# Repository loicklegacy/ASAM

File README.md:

# ASAM
Athmospheric Sensor Array Module

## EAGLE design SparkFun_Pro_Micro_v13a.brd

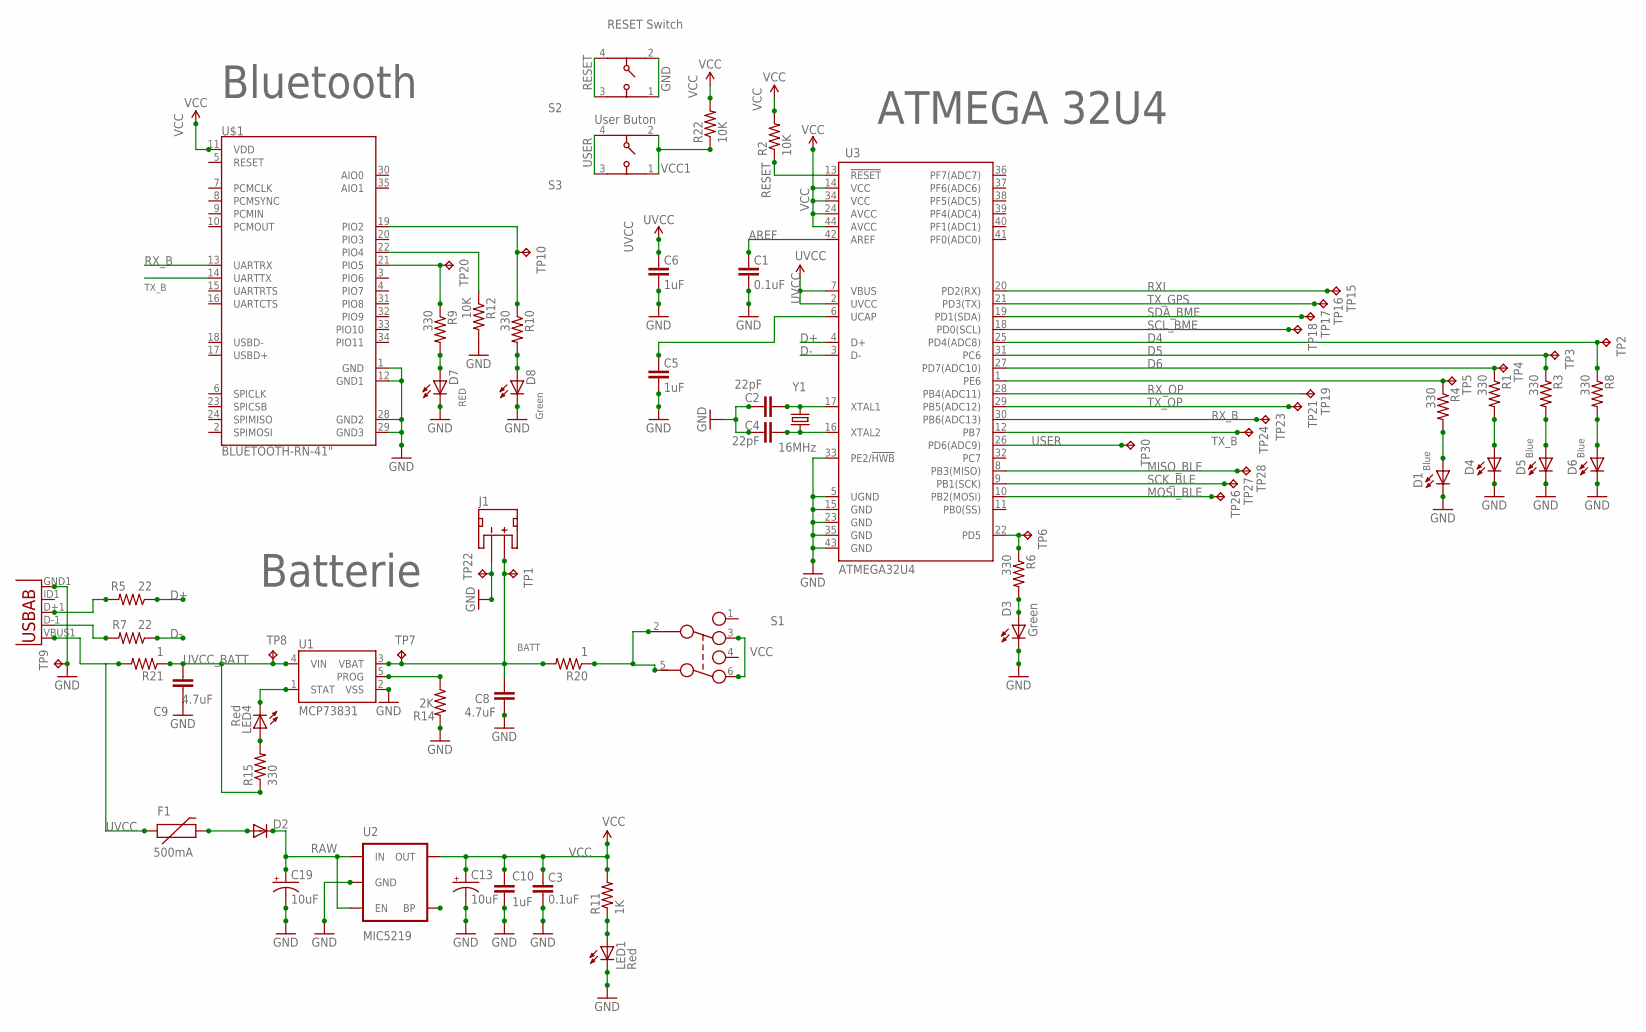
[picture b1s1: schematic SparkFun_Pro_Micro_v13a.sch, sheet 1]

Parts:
C1, C3: 0.1uF; 0603-CAP
C2, C4: 22pF; 0603-CAP
C5, C6, C10: 1uF; 0603-CAP
C8, C9: 4.7uF; 0603-CAP
C13, C19: 10uF; EIA3216
D1, D4, D5, D6, D7, D8: Yellow; LED-0603
D2: DIODESOD; SOD-323
D3: Green; LED-0603
F1: 500mA; PTC-1206
J1: JST_2MM_MALE; JST-2-SMD
LED1, LED4: Red; LED-0603
R1, R3, R4, R6, R8, R9, R10, R15: 330; 0603-RES
R2, R12, R22: 10K; 0603-RES
R5, R7: 22; 0603-RES
R11: 1K; 0603-RES
R14: 2K; 0603-RES
R20, R21: 1; 0603-RES
S1: 452403012014
S2, S3: 434153017835
TP1, TP2, TP3, TP4, TP5, TP6, TP7, TP8, TP10, TP15, TP16, TP17, TP18, TP19, TP20, TP21, TP22, TP26, TP27, TP28, TP30: TPTP08SQ; TP08SQ
TP9: TPTP17SQ; TP17SQ
TP23, TP24: TPTP20SQ; TP20SQ
U1: MCP73831; SOT23-5
U2: MIC5219; SOT23-5
U3: ATMEGA32U4; QFN-44-NOPAD_1:1-OUTFAKES
U$1: BLUETOOTH-RN-41"; RN41
X1: USB-ABIN&OUT; USB-AB-MICRO-SMD-V03-IN&OUT
Y1: 16MHz; CRYSTAL-SMD-5X3

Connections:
AREF: C1.2, U3.42 (AREF)
D1: R9.1, TP20.TP, U$1.21 (PIO5)
D2: R10.1, TP10.TP, U$1.19 (PIO2)
D4: R8.1, TP2.TP, U3.25 (PD4(ADC8))
D5: R3.1, TP3.TP, U3.31 (PC6)
D6: R1.1, TP4.TP, U3.27 (PD7(ADC10))
D14: R4.1, TP5.TP, U3.1 (PE6)
D+: R5.1, U3.4 (D+)
D-: R7.1, U3.3 (D-)
GND: C1.1, C2.2, C3.1, C4.2, C5.1, C6.1, C8.2, C9.2, C10.2, C13.C (-), C19.C (-), D1.C, D3.C, D4.C, D5.C, D6.C, D7.C, D8.C, J1.1 (-), LED1.C, R12.2, R14.2, S2.1, S2.2, TP9.TP, TP22.TP, U1.2 (VSS), U2.2 (GND), U3.5 (UGND), U3.15 (GND), U3.23 (GND), U3.33 (PE2/!HWB), U3.35 (GND), U3.43 (GND), U$1.1 (GND), U$1.12 (GND1), U$1.28 (GND2), U$1.29 (GND3), X1.GND1 (GND); also elsewhere on the board
MISO_BLE: TP28.TP, U3.8 (PB3(MISO)); also elsewhere on the board
MOSI_BLE: TP26.TP, U3.10 (PB2(MOSI)); also elsewhere on the board
unnamed: C4.1, U3.16 (XTAL2), Y1.1
unnamed: C2.1, U3.17 (XTAL1), Y1.3 (2)
unnamed: D2.2 (A), F1.2
unnamed: C5.2, U3.6 (UCAP)
unnamed: D1.A, R4.2
unnamed: R7.2, X1.D-1 (D-)
unnamed: D4.A, R1.2
unnamed: R5.2, X1.D+1 (D+)
unnamed: D5.A, R3.2
unnamed: D6.A, R8.2
unnamed: D3.A, R6.2
unnamed: R12.1, U$1.22 (PIO4)
unnamed: D7.A, R9.2
unnamed: D8.A, R10.2
unnamed: R14.1, U1.5 (PROG)
unnamed: LED4.A, R15.2
unnamed: LED4.C, U1.1 (STAT)
unnamed: LED1.A, R11.1
unnamed: R20.1, S1.2, S1.5
RAW: C19.A (+), D2.1 (C), U2.1 (IN), U2.3 (EN)
RESET: R2.1, S2.3, S2.4, U3.13 (!RESET)
RXI: TP15.TP, U3.20 (PD2(RX)); also elsewhere on the board
RX_B: TP23.TP, U3.30 (PB6(ADC13)), U$1.13 (UARTRX)
RX_OP: TP19.TP, U3.28 (PB4(ADC11)); also elsewhere on the board
SCK_BLE: TP27.TP, U3.9 (PB1(SCK)); also elsewhere on the board
SCL_BME: TP18.TP, U3.18 (PD0(SCL)); also elsewhere on the board
SDA_BME: TP17.TP, U3.19 (PD1(SDA)); also elsewhere on the board
TXLED: R6.1, TP6.TP, U3.22 (PD5)
TX_B: TP24.TP, U3.12 (PB7), U$1.14 (UARTTX)
TX_GPS: TP16.TP, U3.21 (PD3(TX)); also elsewhere on the board
TX_OP: TP21.TP, U3.29 (PB5(ADC12)); also elsewhere on the board
USER: S3.3, S3.4, TP30.TP, U3.26 (PD6(ADC9))
UVCC: C6.2, F1.1, R21.2, U3.2 (UVCC), U3.7 (VBUS), X1.VBUS1 (VBUS)
UVCC_BATT: C9.1, R15.1, R21.1, TP8.TP, U1.4 (VIN)
VBATT: C8.1, J1.2 (+), R20.2, TP1.TP, TP7.TP, U1.3 (VBAT)
VCC: C3.2, C10.1, C13.A (+), R2.2, R11.2, R22.2, S1.3, S1.6, U2.5 (OUT), U3.14 (VCC), U3.24 (AVCC), U3.34 (VCC), U3.44 (AVCC), U$1.11 (VDD); also elsewhere on the board
VCC1: R22.1, S3.1, S3.2

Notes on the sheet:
ATMEGA 32U4
BATT
Blue
RED
Green
Bluetooth
Batterie
RESET Switch
User Buton

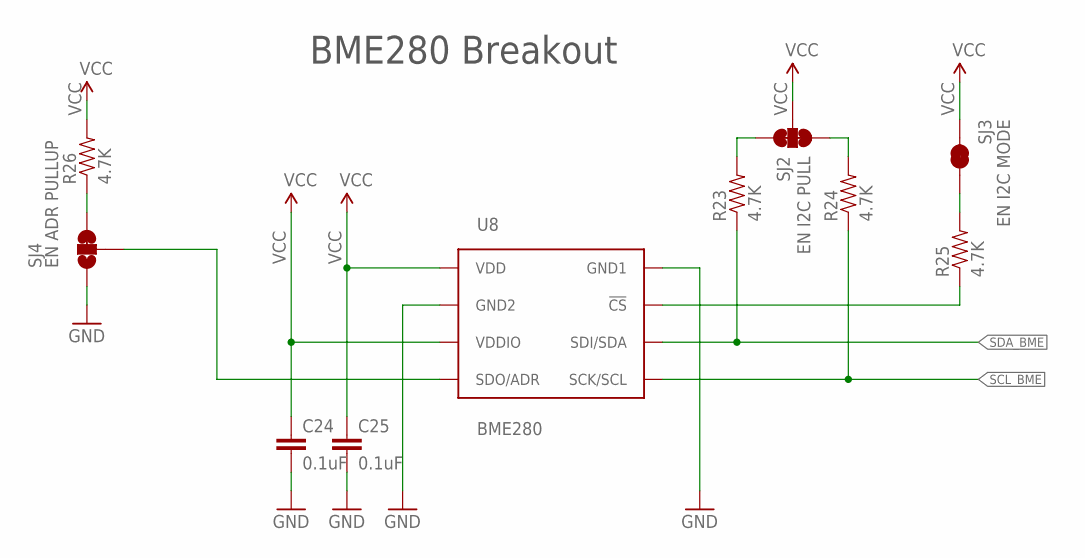
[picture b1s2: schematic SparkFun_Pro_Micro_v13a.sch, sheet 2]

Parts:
C24, C25: 0.1uF; 0603-CAP@2
R23, R24, R25, R26: 4.7K; 0603-RES@2
SJ2: EN I2C PULL; PAD-JUMPER-3-3OF3_NC_BY_TRACE_YES_SILK_FULL_BOX
SJ3: EN I2C MODE; PAD-JUMPER-2-NC_BY_TRACE_YES_SILK
SJ4: EN ADR PULLUP; PAD-JUMPER-3-2OF3_NC_BY_TRACE_YES_SILK_FULL_BOX
U8: BME280; BME280_LGA

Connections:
!CS: R25.1, U8.P$2 (!CS)
GND: C24.2, C25.2, SJ4.1, U8.P$1 (GND1), U8.P$7 (GND2); also elsewhere on the board
unnamed: R23.2, SJ2.3
unnamed: R24.2, SJ2.1
unnamed: R25.2, SJ3.1
unnamed: R26.1, SJ4.3
SCL_BME: R24.1, U8.P$4 (SCK/SCL); also elsewhere on the board
SDA_BME: R23.1, U8.P$3 (SDI/SDA); also elsewhere on the board
SDO/ADR: SJ4.2, U8.P$5 (SDO/ADR)
VCC: C24.1, C25.1, R26.2, SJ2.2, SJ3.2, U8.P$6 (VDDIO), U8.P$8 (VDD); also elsewhere on the board

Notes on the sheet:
BME280 Breakout

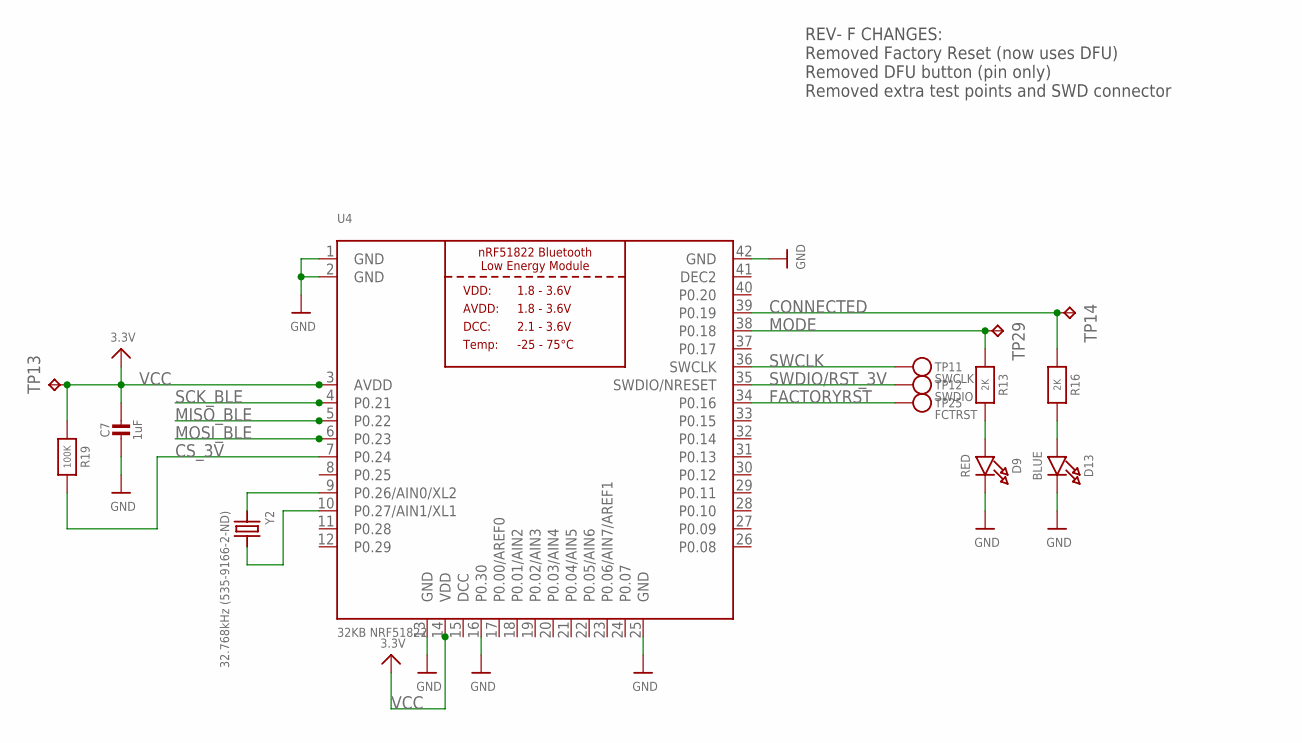
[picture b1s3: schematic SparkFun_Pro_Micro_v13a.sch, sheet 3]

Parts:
C7: 1uF; 0805_10MGAP
D9: RED; CHIPLED_0805_NOOUTLINE
D13: BLUE; CHIPLED_0805_NOOUTLINE
R13, R16: 2K; _0805MP
R19: 100K; _0805MP
TP11: SWCLK; PAD-1.5X2.0
TP12: SWDIO; PAD-1.5X2.0
TP13, TP14, TP29: TPTP08SQ; TP08SQ
TP25: FCTRST; PAD-1.5X2.0
U4: 32KB NRF51822; BLE_MODULE_RAYTAC_MDBT40
Y2: 32.768kHz (535-9166-2-ND); CRYSTAL_CYL_2X6MM_SMT

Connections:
CONNECTED: R16.1, TP14.TP, U4.39 (P0.19)
CS_3V: R19.2, U4.7 (P0.24)
DCC: U4.15 (DCC)
DEC2: U4.41 (DEC2)
FACTORYRST: TP25.P$1, U4.34 (P0.16)
GND: C7.2, D9.C, D13.C, U4.1 (GND), U4.2 (GND), U4.13 (GND), U4.16 (P0.30), U4.25 (GND), U4.42 (GND); also elsewhere on the board
MISO_BLE: U4.5 (P0.22); also elsewhere on the board
MODE: R13.1, TP29.TP, U4.38 (P0.18)
MOSI_BLE: U4.6 (P0.23); also elsewhere on the board
unnamed: D9.A, R13.2
unnamed: D13.A, R16.2
unnamed: U4.9 (P0.26/AIN0/XL2), Y2.1
unnamed: U4.10 (P0.27/AIN1/XL1), Y2.2
SCK_BLE: U4.4 (P0.21); also elsewhere on the board
SWCLK: TP11.P$1, U4.36 (SWCLK)
SWDIO/RST_3V: TP12.P$1, U4.35 (SWDIO/NRESET)
VCC: C7.1, R19.1, TP13.TP, U4.3 (AVDD), U4.14 (VDD); also elsewhere on the board

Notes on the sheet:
REV- F CHANGES: Removed Factory Reset (now uses DFU) Removed DFU button (pin only) Removed extra test points and SWD connector

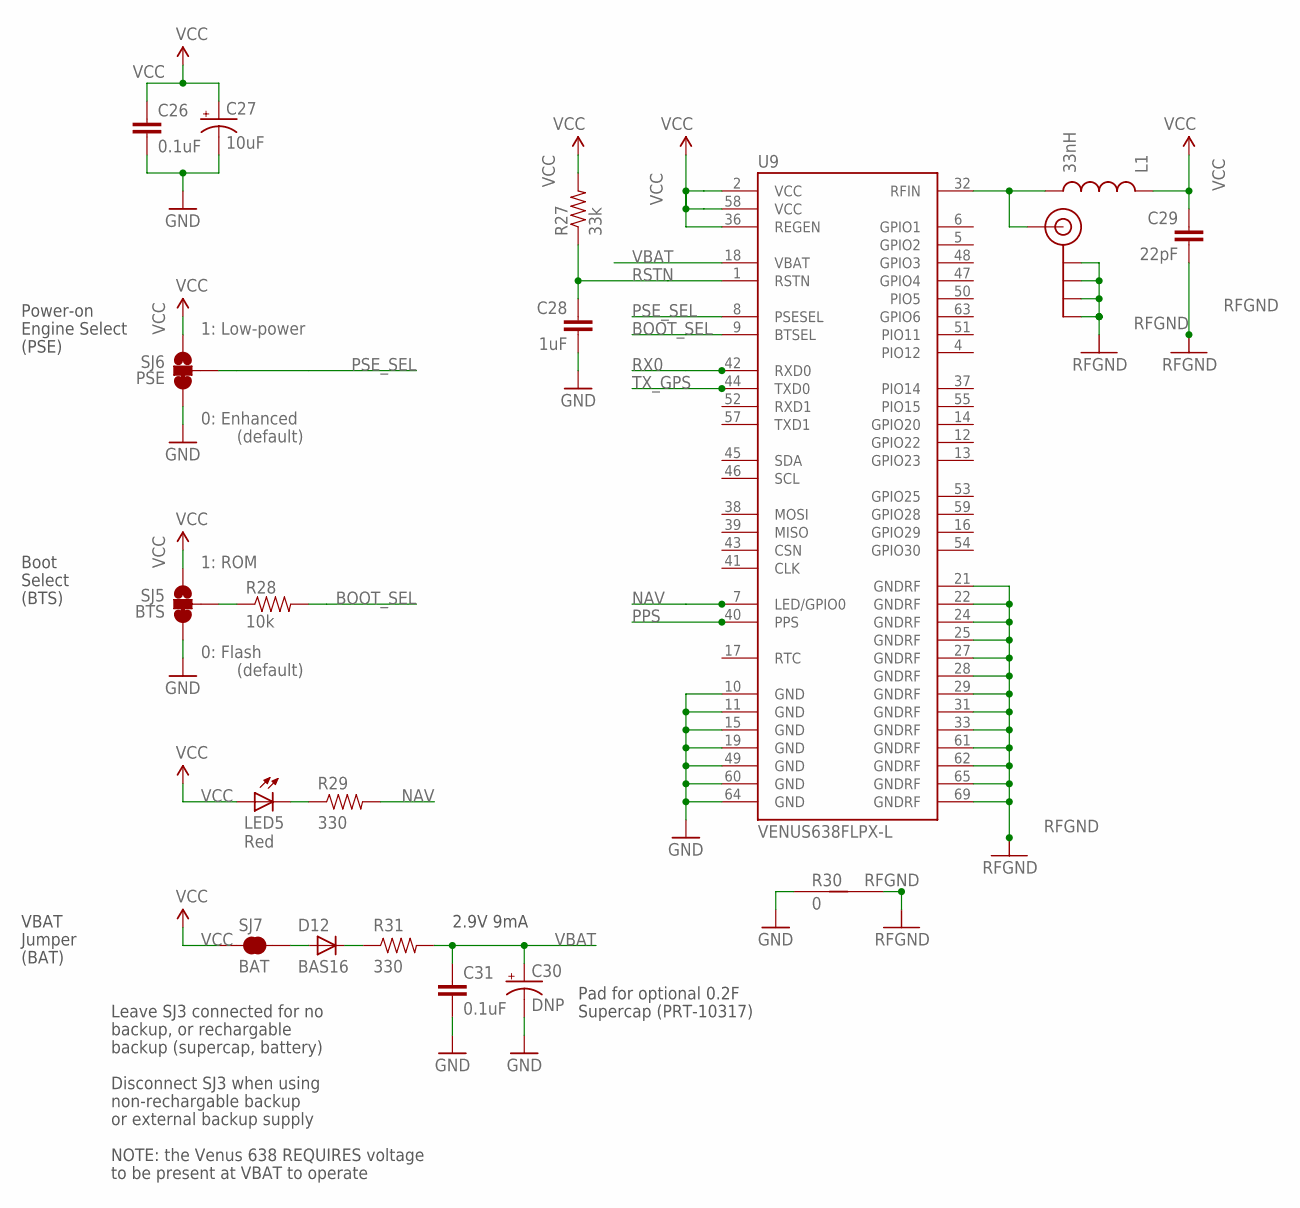
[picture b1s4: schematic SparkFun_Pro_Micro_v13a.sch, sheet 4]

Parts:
C26, C31: 0.1uF; 0402-CAP
C27: 10uF; EIA3216
C28: 1uF; 0402-CAP
C29: 22pF; 0402-CAP
C30: DNP; EN_J2
D12: BAS16; SOD-323
JP10: SMA_EDGE; SMA-EDGE
L1: 33nH; C0402
LED5: Red; LED-0603
R27: 33k; 0402-RES
R28: 10k; 0402-RES
R29, R31: 330; 0402-RES
R30: 0; GND-JUMP
SJ5: BTS; SJ_3_PASTE2&3
SJ6: PSE; SJ_3_PASTE2&3
SJ7: BAT; SJ_2S
U9: VENUS638FLPX-L; VENUS638FLPX

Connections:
ANT: JP10.SIG (SIGNAL), L1.2, U9.32 (RFIN)
BOOT_SEL: R28.2, U9.9 (BTSEL)
GND: C26.2, C27.C (-), C28.2, C30.-, C31.2, R30.1, SJ5.3, SJ6.3, U9.10 (GND), U9.11 (GND), U9.15 (GND), U9.19 (GND), U9.49 (GND), U9.60 (GND), U9.64 (GND); also elsewhere on the board
unnamed: LED5.C, R29.1
unnamed: R28.1, SJ5.2
unnamed: D12.2 (A), SJ7.2
unnamed: D12.1 (C), R31.1
NAV: R29.2, U9.7 (LED/GPIO0)
PPS: U9.40 (PPS)
PSE_SEL: SJ6.2, U9.8 (PSESEL)
RFGND: C29.2, JP10.GND@0 (GND), JP10.GND@1 (GND), JP10.GND@2 (GND), JP10.GND@3 (GND), R30.2, U9.21 (GNDRF), U9.22 (GNDRF), U9.24 (GNDRF), U9.25 (GNDRF), U9.27 (GNDRF), U9.28 (GNDRF), U9.29 (GNDRF), U9.31 (GNDRF), U9.33 (GNDRF), U9.61 (GNDRF), U9.62 (GNDRF), U9.65 (GNDRF), U9.69 (GNDRF)
RSTN: C28.1, R27.1, U9.1 (RSTN)
RX0: U9.42 (RXD0)
TX_GPS: U9.44 (TXD0); also elsewhere on the board
VBAT: C30.+, C31.1, R31.2, U9.18 (VBAT)
VCC: C26.1, C27.A (+), C29.1, L1.1, LED5.A, R27.2, SJ5.1, SJ6.1, SJ7.1, U9.2 (VCC), U9.36 (REGEN), U9.58 (VCC); also elsewhere on the board

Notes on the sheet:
RFGND
1: Low-power
0: Enhanced
0: Flash
1: ROM
(default)
Supercap (PRT-10317)
Pad for optional 0.2F
2.9V 9mA
Power-on
Engine Select
Boot
Select
(PSE)
(BTS)
VBAT
Jumper
(BAT)
Leave SJ3 connected for no
backup, or rechargable
backup (supercap, battery)
Disconnect SJ3 when using
non-rechargable backup
or external backup supply
NOTE: the Venus 638 REQUIRES voltage
to be present at VBAT to operate

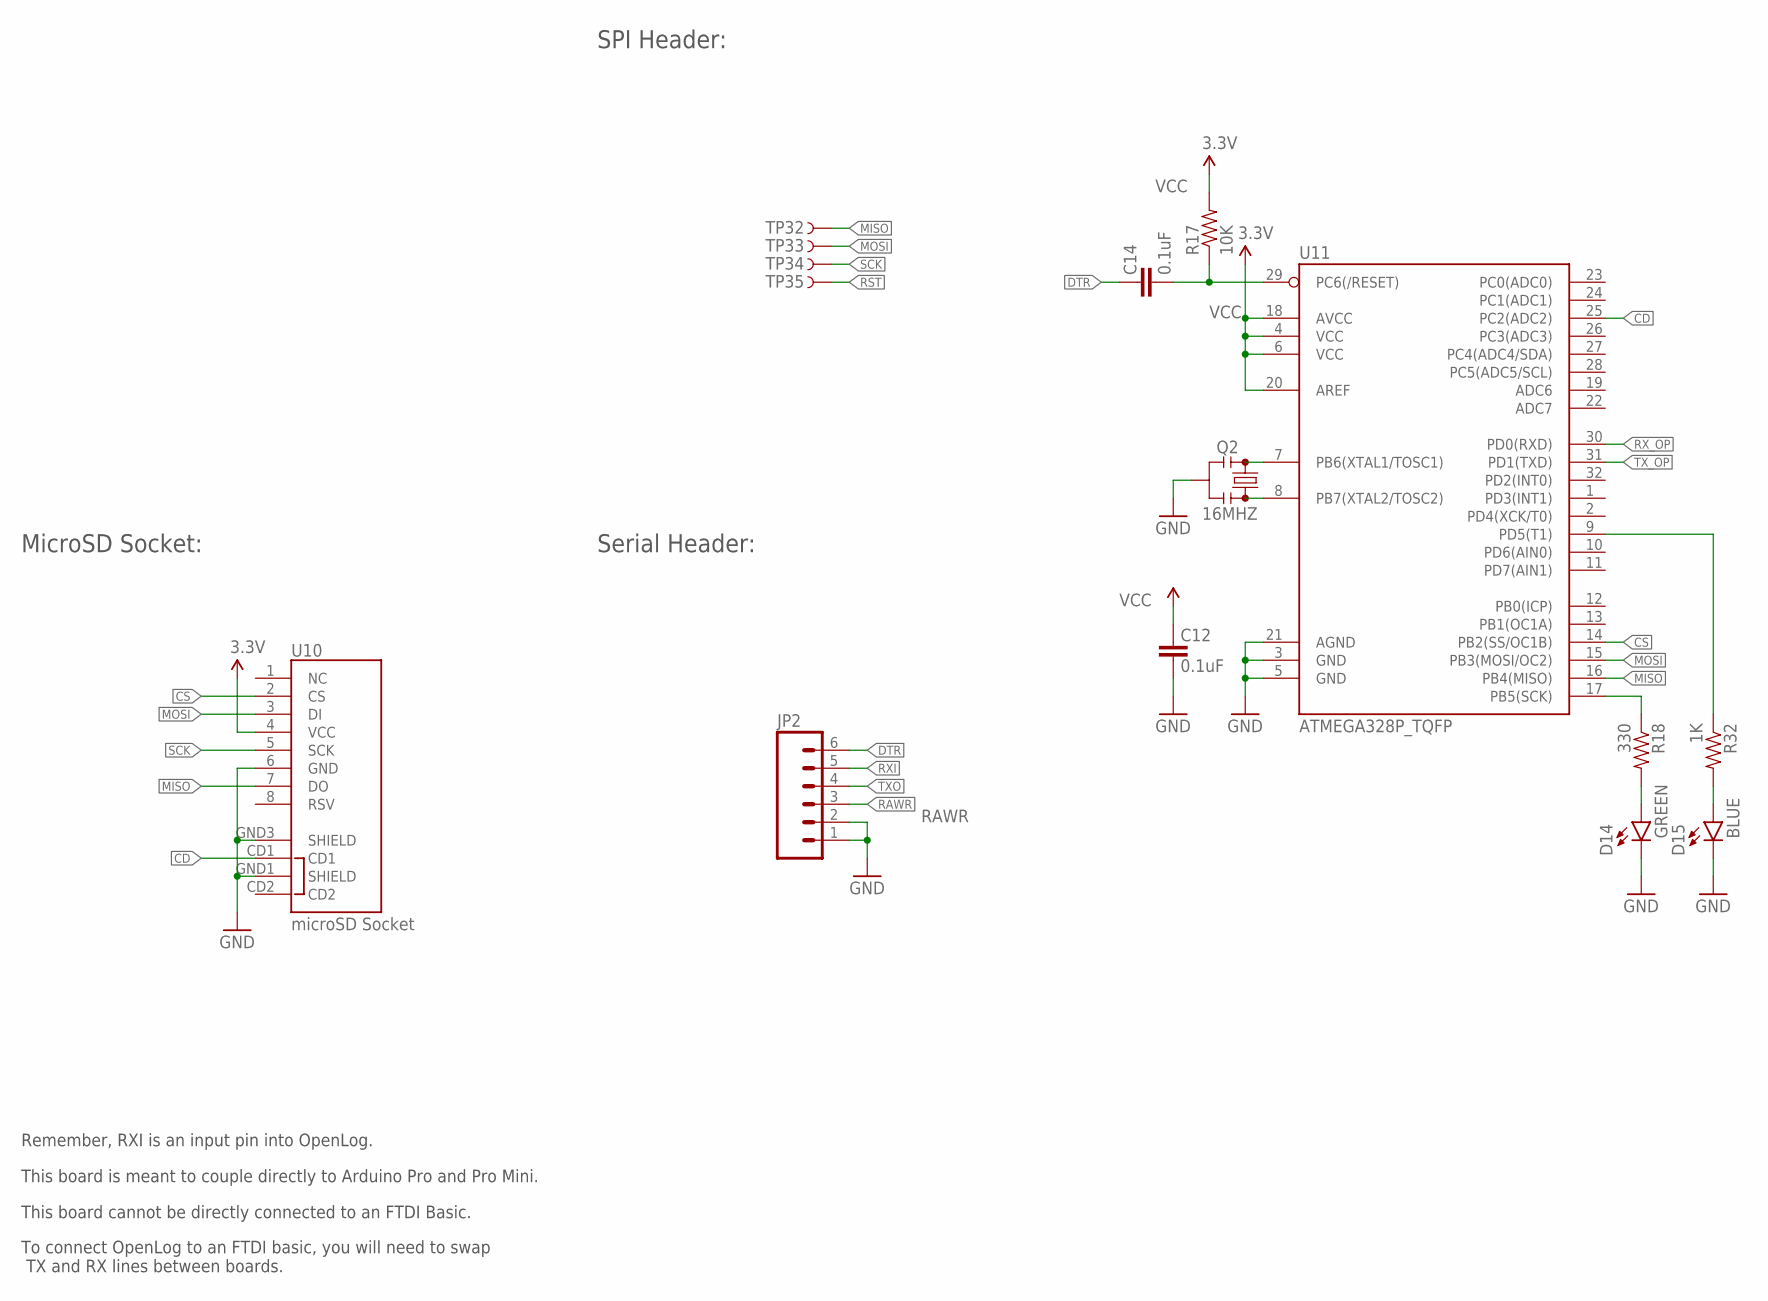
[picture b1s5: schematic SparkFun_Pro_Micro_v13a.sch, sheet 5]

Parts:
C12, C14: 0.1uF; 0603-CAP
D14: GREEN; LED-0603
D15: BLUE; LED-0603
JP2: M06NO_SILK_FEMALE_PTH; 1X06_NO_SILK
Q2: 16MHZ; RESONATOR-SMD
R17: 10K; 0603-RES
R18: 330; 0603-RES
R32: 1K; 0603-RES
TP32, TP33, TP34, TP35: TEST-POINT3; PAD.03X.03
U10: microSD Socket; MICROSD_1:1
U11: ATMEGA328P_TQFP; TQFP32-08

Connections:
3.3V: U10.4 (VCC)
CD: U10.CD1, U11.25 (PC2(ADC2))
CS: U10.2 (CS), U11.14 (PB2(SS/OC1B))
DTR: C14.2, JP2.6
GND: C12.1, D14.C, D15.C, JP2.1, JP2.2, Q2.2, U10.6 (GND), U10.GND1 (SHIELD), U10.GND3 (SHIELD), U11.3 (GND), U11.5 (GND), U11.21 (AGND); also elsewhere on the board
MISO: TP32.P$1, U10.7 (DO), U11.16 (PB4(MISO))
MOSI: TP33.P$1, U10.3 (DI), U11.15 (PB3(MOSI/OC2))
unnamed: D14.A, R18.2
unnamed: Q2.1, U11.8 (PB7(XTAL2/TOSC2))
unnamed: Q2.3, U11.7 (PB6(XTAL1/TOSC1))
unnamed: D15.A, R32.2
unnamed: R32.1, U11.9 (PD5(T1))
RAWR: JP2.3
RST: C14.1, R17.1, TP35.P$1, U11.29 (PC6(/RESET))
RXI: JP2.5; also elsewhere on the board
RX_OP: U11.30 (PD0(RXD)); also elsewhere on the board
SCK: R18.1, TP34.P$1, U10.5 (SCK), U11.17 (PB5(SCK))
TXO: JP2.4
TX_OP: U11.31 (PD1(TXD)); also elsewhere on the board
VCC: C12.2, R17.2, U11.4 (VCC), U11.6 (VCC), U11.18 (AVCC), U11.20 (AREF); also elsewhere on the board

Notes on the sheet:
Remember, RXI is an input pin into OpenLog.
This board is meant to couple directly to Arduino Pro and Pro Mini.
This board cannot be directly connected to an FTDI Basic.
To connect OpenLog to an FTDI basic, you will need to swap TX and RX lines between boards.
Serial Header:
MicroSD Socket:
SPI Header:

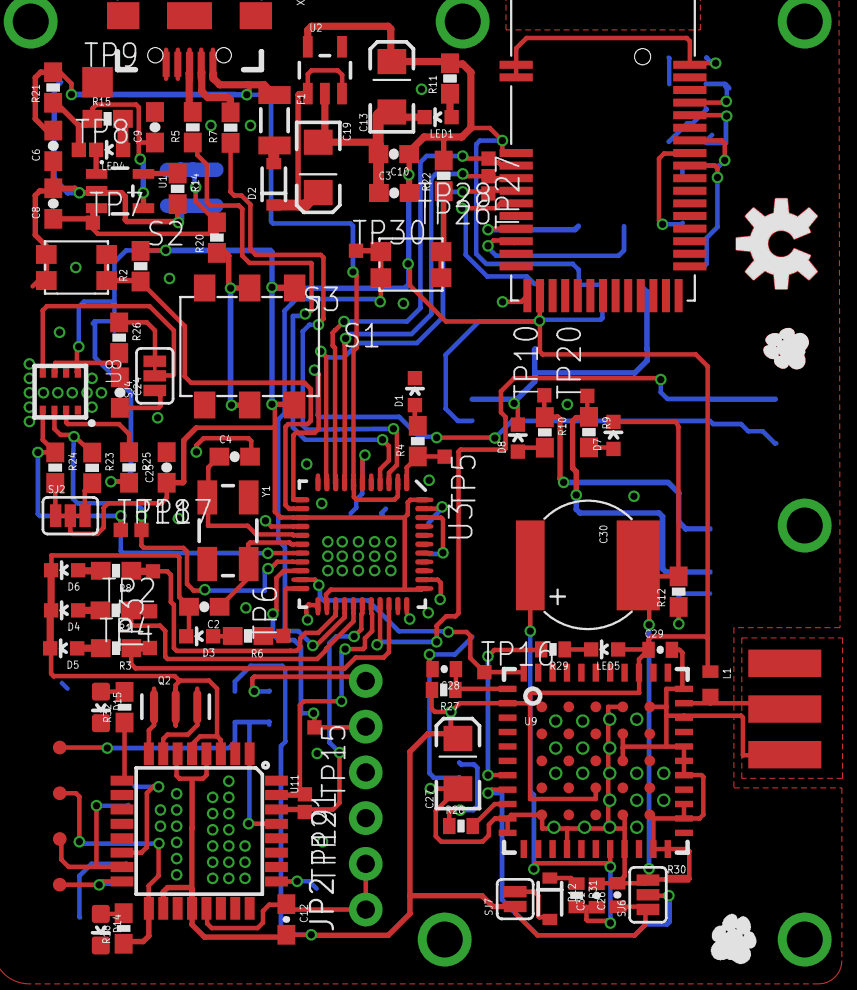
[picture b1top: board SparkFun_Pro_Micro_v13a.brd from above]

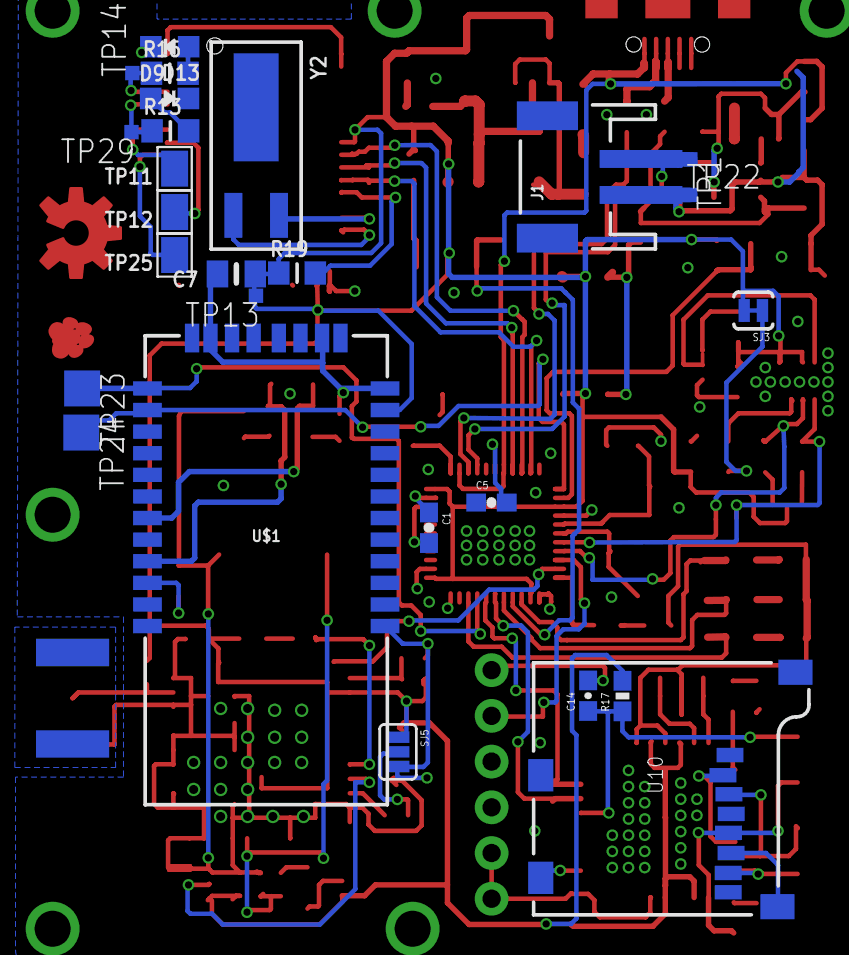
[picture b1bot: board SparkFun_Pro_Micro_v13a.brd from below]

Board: 2 copper layers, 133 parts (26 on the bottom side), 88 nets.

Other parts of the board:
U$3: OSHW-LOGO-M_COPPER
U$4: OSHW-LOGO-M

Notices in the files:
parts and their libraries:
SparkFun-Capacitors: Licensing: Creative Commons ShareAlike 4.0 International - https://creativecommons.org/licenses/by-sa/4.0
Switches_rev16a: Copyright: Würth Elektronik
SparkFun-Aesthetics: Licensing: CC v3.0 Share-Alike You are welcome to use this library for commercial purposes.
